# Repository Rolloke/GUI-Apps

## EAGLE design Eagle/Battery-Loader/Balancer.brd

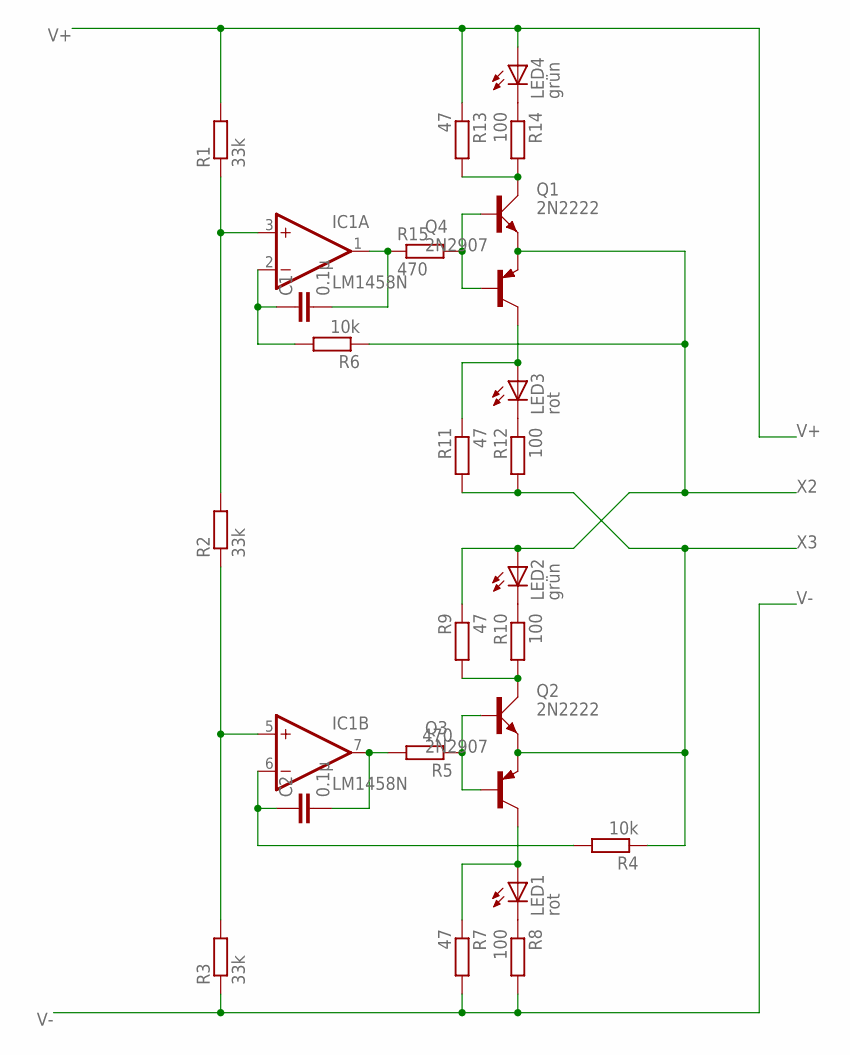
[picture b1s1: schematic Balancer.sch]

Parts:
C1, C2: 0.1µ; C050-025X075
IC1: LM1458N; DIL08
LED1, LED3: rot; LED5MM
LED2, LED4: grün; LED5MM
Q1, Q2: 2N2222; TO18A
Q3, Q4: 2N2907; TO18
R1, R2, R3: 33k; 0204/5
R4, R6: 10k; 0204/5
R5, R15: 470; 0204/5
R7, R9, R11, R13: 47; 0204/5
R8, R10, R12, R14: 100; 0204/5

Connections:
unnamed: C1.2, IC1.1 (OUT), R15.1
unnamed: LED4.K (C), R14.1
unnamed: Q1.C, R13.2, R14.2
unnamed: LED3.K (C), R12.1
unnamed: LED2.K (C), R10.1
unnamed: Q2.C, R9.2, R10.2
unnamed: LED1.K (C), R8.1
unnamed: IC1.5 (+IN), R2.1, R3.2
unnamed: IC1.3 (+IN), R1.1, R2.2
unnamed: C1.1, IC1.2 (-IN), R6.2
unnamed: LED3.A, Q4.3 (C), R11.1
unnamed: Q1.B, Q4.2 (B), R15.2
unnamed: Q2.B, Q3.2 (B), R5.1
unnamed: C2.2, IC1.7 (OUT), R5.2
unnamed: C2.1, IC1.6 (-IN), R4.2
unnamed: LED1.A, Q3.3 (C), R7.1
V+: IC1.8 (V+), LED4.A, R1.2, R13.1
V-: IC1.4 (V-), R3.1, R7.2, R8.2
X2: LED2.A, Q1.E, Q4.1 (E), R6.1, R9.1
X3: Q2.E, Q3.1 (E), R4.1, R11.2, R12.2

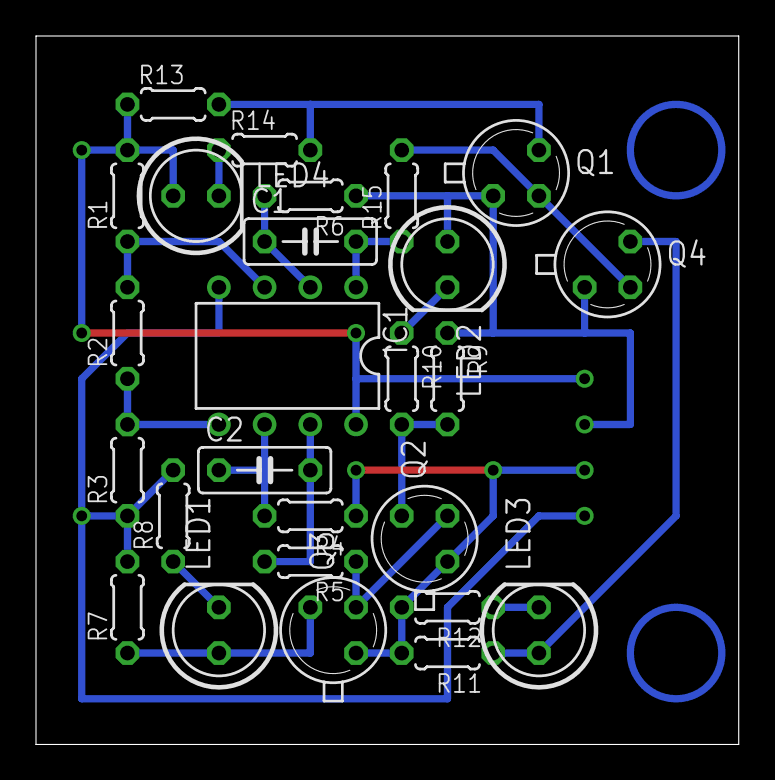
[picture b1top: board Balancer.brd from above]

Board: 2 copper layers, 39.0 x 39.4 mm, 26 parts (0 on the bottom side), 20 nets.

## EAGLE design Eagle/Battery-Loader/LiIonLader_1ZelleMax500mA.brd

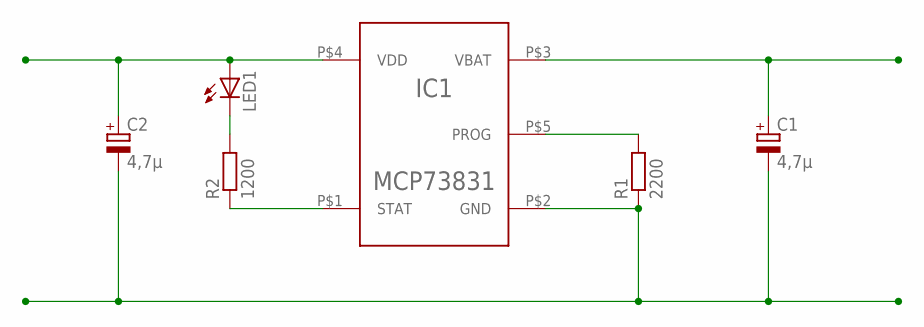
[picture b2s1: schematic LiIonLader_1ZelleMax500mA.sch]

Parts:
C1, C2: 4,7µ; E1,8-4
IC1: MCP73831; SOT-23-5
LED1: LED3MM
R1: 2200; 0204/5
R2: 1200; 0204/5

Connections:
GND: C1.-, C2.-, IC1.P$2 (GND), R1.1
unnamed: LED1.K (C), R2.2
PROG: IC1.P$5 (PROG), R1.2
STAT: IC1.P$1 (STAT), R2.1
VBAT: C1.+, IC1.P$3 (VBAT)
VDD: C2.+, IC1.P$4 (VDD), LED1.A

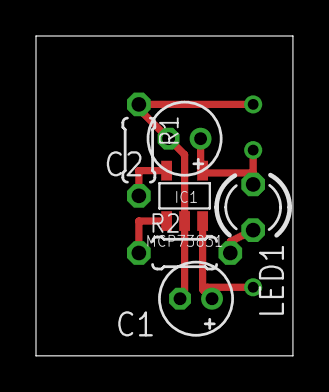
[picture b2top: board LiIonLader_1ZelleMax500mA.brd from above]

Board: 2 copper layers, 14.3 x 17.8 mm, 6 parts (0 on the bottom side), 6 nets.

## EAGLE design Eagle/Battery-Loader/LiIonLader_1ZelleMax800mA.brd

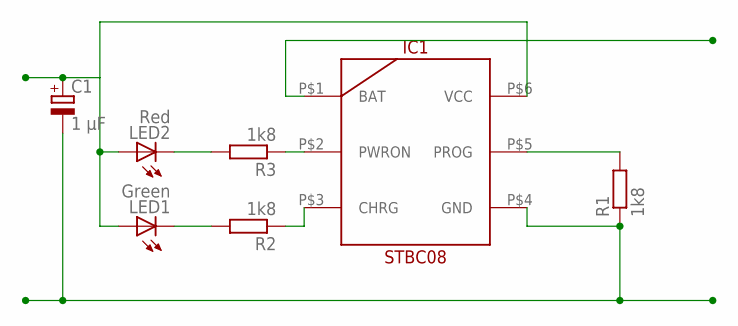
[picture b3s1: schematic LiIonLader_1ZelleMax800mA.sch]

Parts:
C1: 1 µF; E1,8-4
IC1: STBC08; DFN6
LED1: Green; LED3MM
LED2: Red; LED3MM
R1, R2, R3: 1k8; 0204/5

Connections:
BAT: IC1.P$1 (BAT)
GND: C1.-, IC1.P$4 (GND), R1.1
unnamed: IC1.P$3 (CHRG), R2.1
unnamed: LED1.K (C), R2.2
unnamed: LED2.K (C), R3.2
PROG: IC1.P$5 (PROG), R1.2
PWRON: IC1.P$2 (PWRON), R3.1
VCC: C1.+, IC1.P$6 (VCC), LED1.A, LED2.A

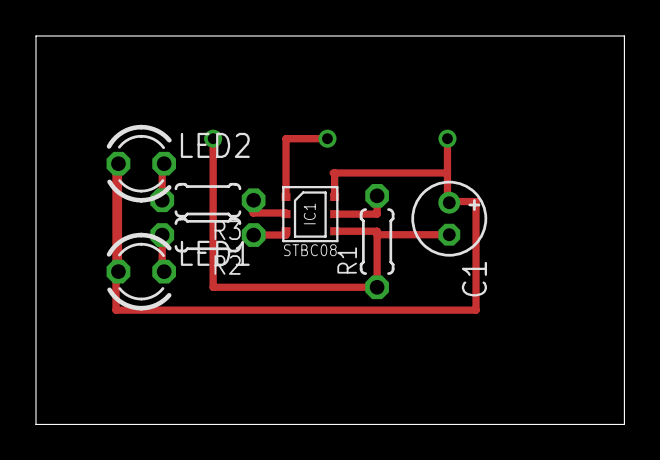
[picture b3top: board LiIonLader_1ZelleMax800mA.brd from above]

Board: 2 copper layers, 32.7 x 21.6 mm, 7 parts (0 on the bottom side), 7 nets.

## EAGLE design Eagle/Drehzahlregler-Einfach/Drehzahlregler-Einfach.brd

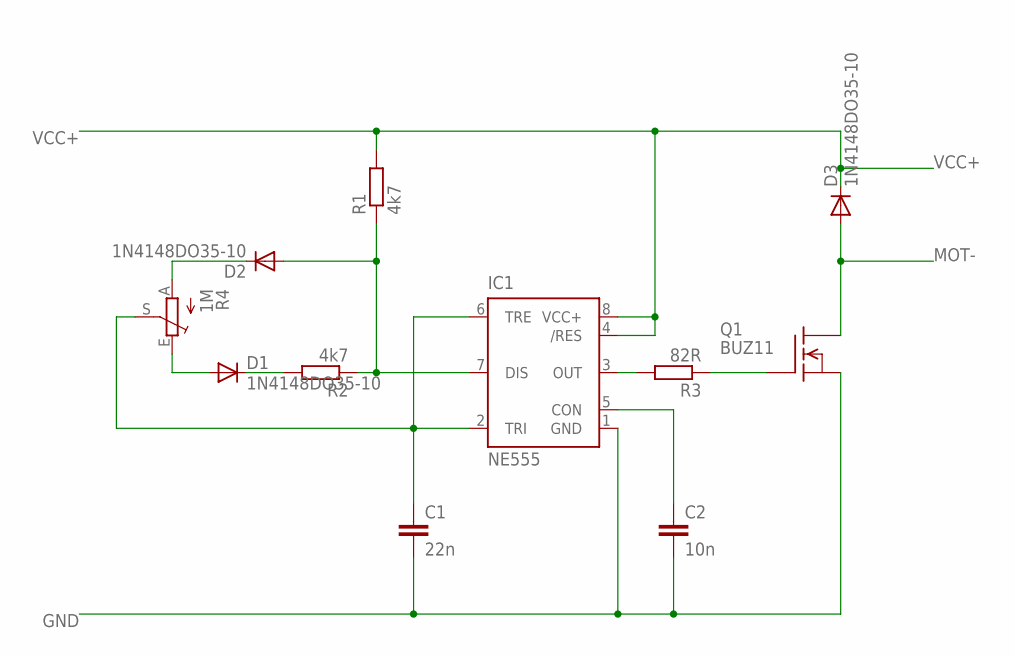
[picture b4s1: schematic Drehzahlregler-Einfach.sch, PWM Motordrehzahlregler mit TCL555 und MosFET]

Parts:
C1: 22n; C5B2.5
C2: 10n; C5B2.5
D1, D2, D3: 1N4148DO35-10; DO35-10
IC1: NE555; DIL-08
Q1: BUZ11; TO220
R1, R2: 4k7; 0207/10
R3: 82R; 0207/10
R4: 1M; CIP20C-4MM

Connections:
GND: C1.2, C2.2, IC1.1 (GND), Q1.3 (S)
MOT-: D3.A, Q1.2 (D)
unnamed: D2.A, IC1.7 (DIS), R1.1, R2.1
unnamed: D2.C, R4.A
unnamed: D1.A, R4.E
unnamed: D1.C, R2.2
unnamed: C1.1, IC1.2 (TRI), IC1.6 (TRE), R4.S
unnamed: C2.1, IC1.5 (CON)
unnamed: IC1.3 (OUT), R3.2
unnamed: Q1.1 (G), R3.1
VCC+: D3.C, IC1.4 (/RES), IC1.8 (VCC+), R1.2

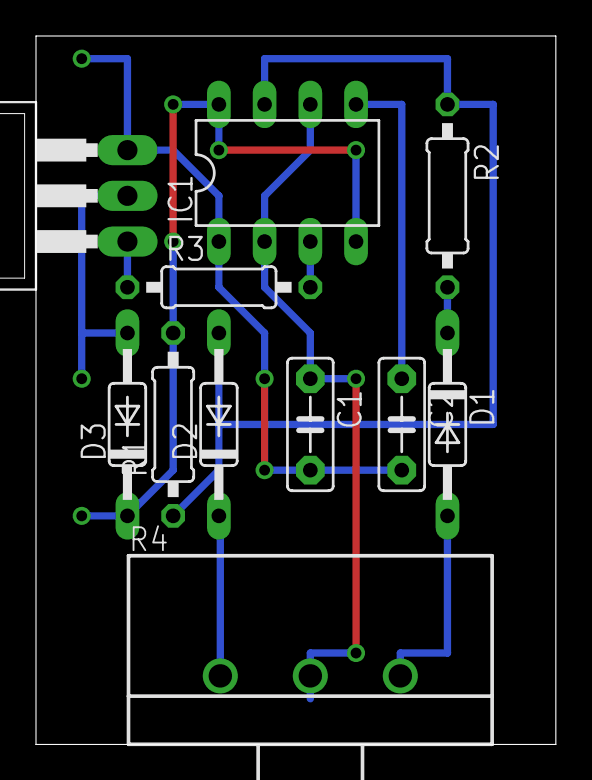
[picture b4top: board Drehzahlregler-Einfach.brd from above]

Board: 2 copper layers, 28.9 x 39.4 mm, 11 parts (0 on the bottom side), 11 nets.

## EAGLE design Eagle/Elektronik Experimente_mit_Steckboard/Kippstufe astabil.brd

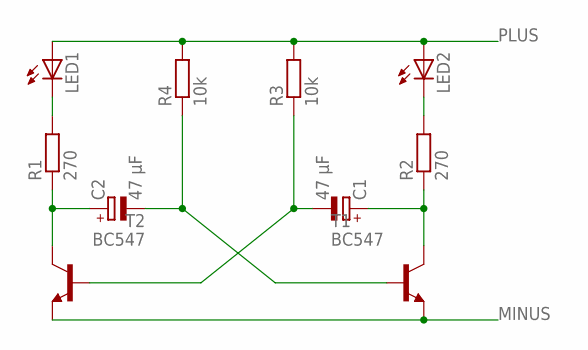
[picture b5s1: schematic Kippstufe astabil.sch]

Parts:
C1, C2: 47 µF; B45181B
LED1, LED2: LED5MM
R1, R2: 270; 0204/7
R3, R4: 10k; 0204/7
T1, T2: BC547; TO92

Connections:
MINUS: T1.1 (E), T2.1 (E)
unnamed: C2.+, R1.1, T2.3 (C)
unnamed: C1.+, R2.1, T1.3 (C)
unnamed: C1.-, R3.1, T2.2 (B)
unnamed: C2.-, R4.1, T1.2 (B)
unnamed: LED2.K (C), R2.2
unnamed: LED1.K (C), R1.2
PLUS: LED1.A, LED2.A, R3.2, R4.2

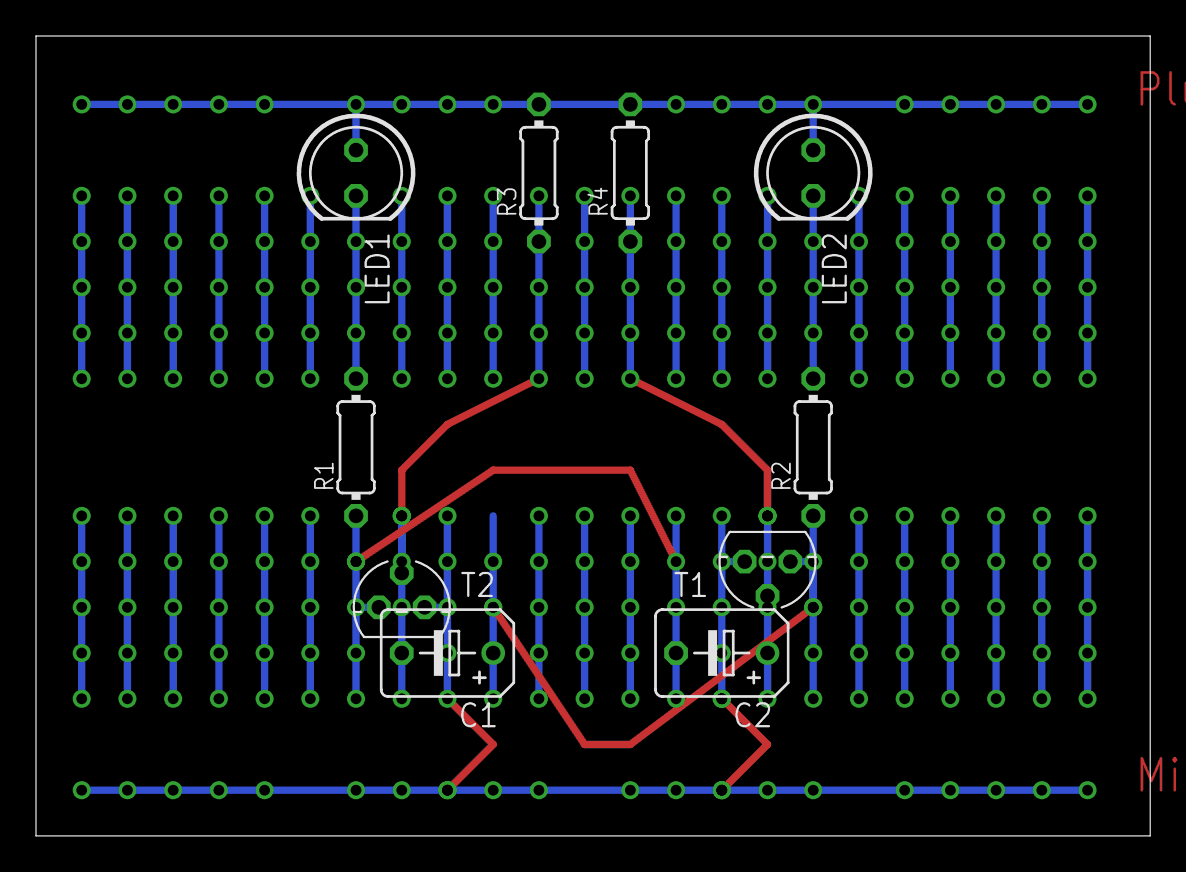
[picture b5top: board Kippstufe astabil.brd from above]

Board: 2 copper layers, 61.9 x 44.4 mm, 10 parts (0 on the bottom side), 8 nets.
